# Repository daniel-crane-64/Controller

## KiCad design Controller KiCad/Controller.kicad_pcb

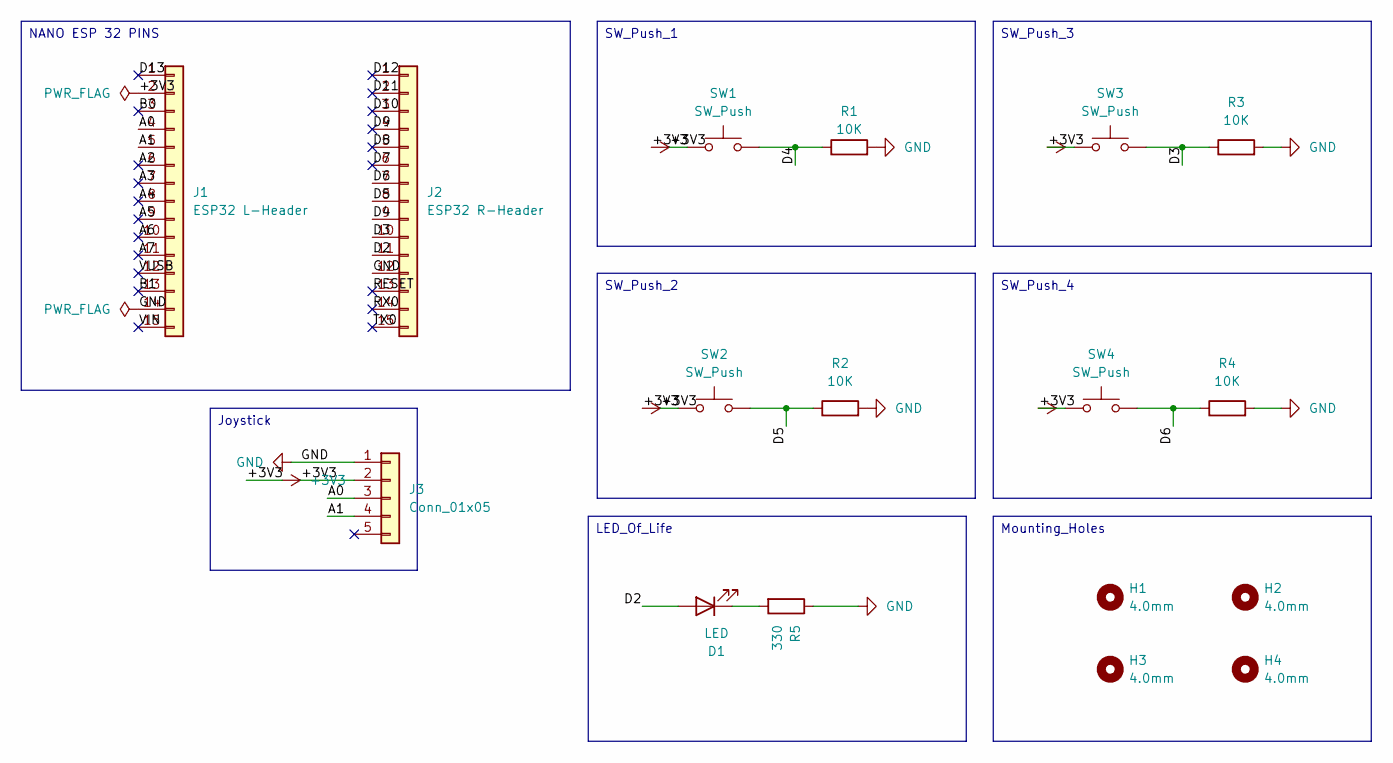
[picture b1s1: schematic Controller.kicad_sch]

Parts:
D1: LED; LED_D5.0mm
H1, H2, H3, H4: 4.0mm; MountingHole_4mm
J1: ESP32 L-Header; PinHeader_1x15_P2.54mm_Vertical
J2: ESP32 R-Header; PinHeader_1x15_P2.54mm_Vertical
J3: Conn_01x05; PinHeader_1x05_P2.54mm_Vertical
R1, R2, R3, R4: 10K; R_Axial_DIN0207_L6.3mm_D2.5mm_P7.62mm_Horizontal
R5: 330; R_Axial_DIN0207_L6.3mm_D2.5mm_P7.62mm_Horizontal
SW1, SW2, SW3, SW4: SW_Push; SW_PUSH_6mm

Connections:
+3V3: J1.2, J3.2, SW1.1, SW2.1, SW3.1, SW4.1
/A0: J1.4, J3.3
/A1: J1.5, J3.4
/A2: J1.6
/A3: J1.7
/A4: J1.8
/A5: J1.9
/A6: J1.10
/A7: J1.11
/B0: J1.3
/B1: J1.13
/D2: D1.2 (A), J2.11
/D3: J2.10, R3.1, SW3.2
/D4: J2.9, R1.1, SW1.2
/D5: J2.8, R2.1, SW2.2
/D6: J2.7, R4.1, SW4.2
/D7: J2.6
/D8: J2.5
/D9: J2.4
/D10: J2.3
/D11: J2.2
/D12: J2.1
/D13: J1.1
/RESET: J2.13
/RX0: J2.14
/TX0: J2.15
/VIN: J1.15
/VUSB: J1.12
GND: J1.14, J2.12, J3.1, R1.2, R2.2, R3.2, R4.2, R5.1
unnamed: D1.1 (K), R5.2

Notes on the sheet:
Mounting_Holes
SW_Push_4
LED_Of_Life
SW_Push_1
NANO ESP 32 PINS
SW_Push_3
Joystick
SW_Push_2

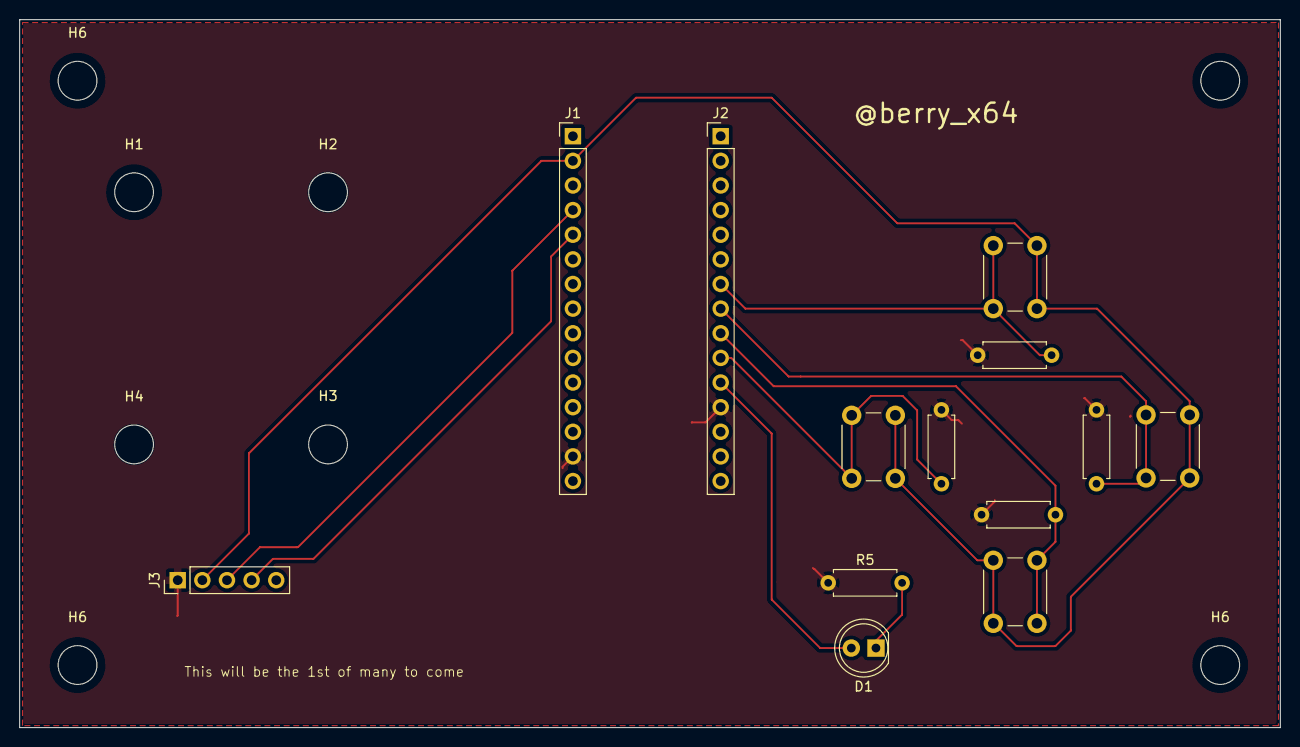
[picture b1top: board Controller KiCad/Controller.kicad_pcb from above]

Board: 2 copper layers, 130.0 x 73.0 mm, 21 parts (0 on the bottom side), 10 nets.

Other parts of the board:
H1#2, H6, H6#2, H6#3: 4.0mm; MountingHole_4mm

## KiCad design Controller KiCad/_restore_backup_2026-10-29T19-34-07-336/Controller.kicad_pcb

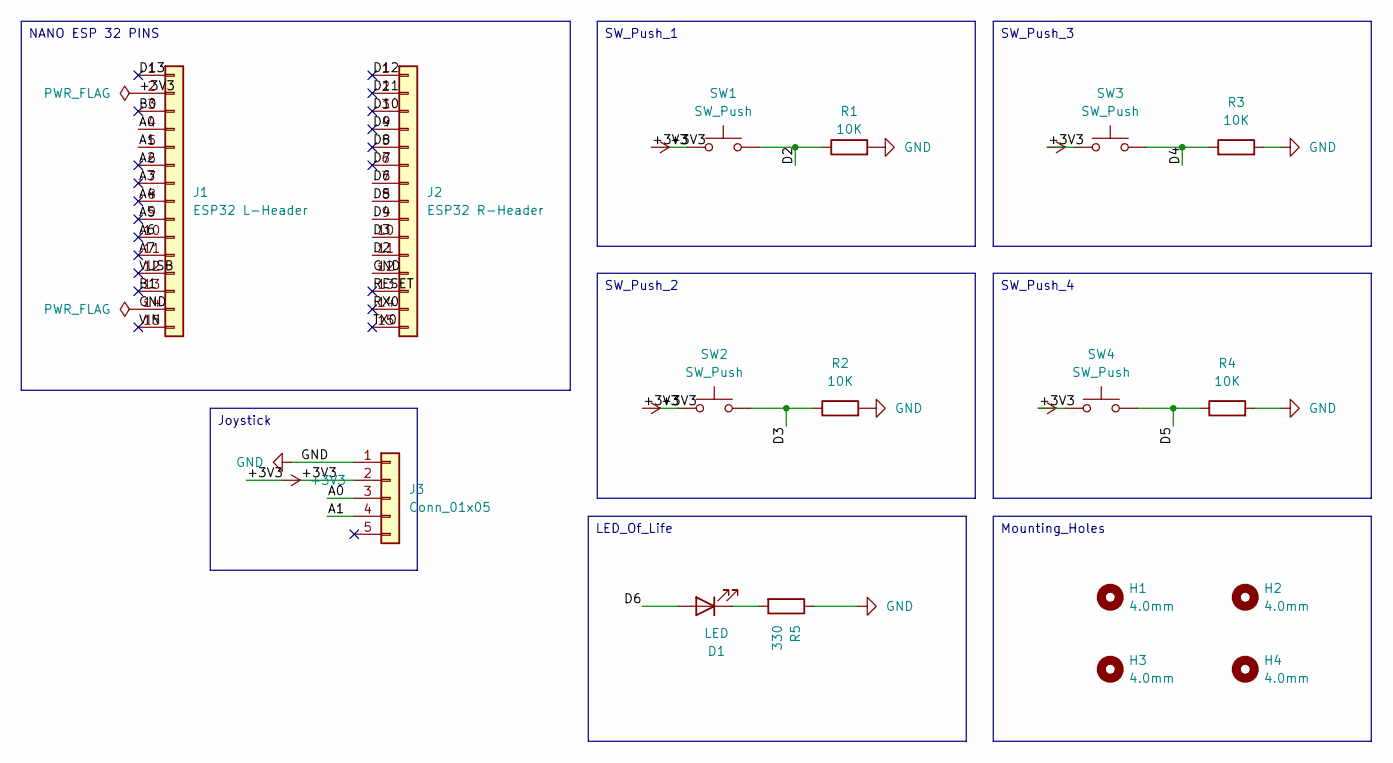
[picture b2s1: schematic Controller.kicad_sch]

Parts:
D1: LED; LED_D5.0mm
H1, H2, H3, H4: 4.0mm; MountingHole_4mm
J1: ESP32 L-Header; PinHeader_1x15_P2.54mm_Vertical
J2: ESP32 R-Header; PinHeader_1x15_P2.54mm_Vertical
J3: Conn_01x05; PinHeader_1x05_P2.54mm_Vertical
R1, R2, R3, R4: 10K; R_Axial_DIN0207_L6.3mm_D2.5mm_P7.62mm_Horizontal
R5: 330; R_Axial_DIN0207_L6.3mm_D2.5mm_P7.62mm_Horizontal
SW1, SW2, SW3, SW4: SW_Push; SW_PUSH_6mm

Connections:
+3V3: J1.2, J3.2, SW1.1, SW2.1, SW3.1, SW4.1
/A0: J1.4, J3.3
/A1: J1.5, J3.4
/A2: J1.6
/A3: J1.7
/A4: J1.8
/A5: J1.9
/A6: J1.10
/A7: J1.11
/B0: J1.3
/B1: J1.13
/D2: J2.11, R1.1, SW1.2
/D3: J2.10, R2.1, SW2.2
/D4: J2.9, R3.1, SW3.2 (2_2)
/D5: J2.8, R4.1, SW4.2 (2_2)
/D6: D1.2 (A), J2.7
/D7: J2.6
/D8: J2.5
/D9: J2.4
/D10: J2.3
/D11: J2.2
/D12: J2.1
/D13: J1.1
/RESET: J2.13
/RX0: J2.14
/TX0: J2.15
/VIN: J1.15
/VUSB: J1.12
GND: J1.14, J2.12, J3.1, R1.2, R2.2, R3.2, R4.2, R5.1
unnamed: D1.1 (K), R5.2

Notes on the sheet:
Mounting_Holes
SW_Push_4
LED_Of_Life
SW_Push_1
NANO ESP 32 PINS
SW_Push_3
Joystick
SW_Push_2

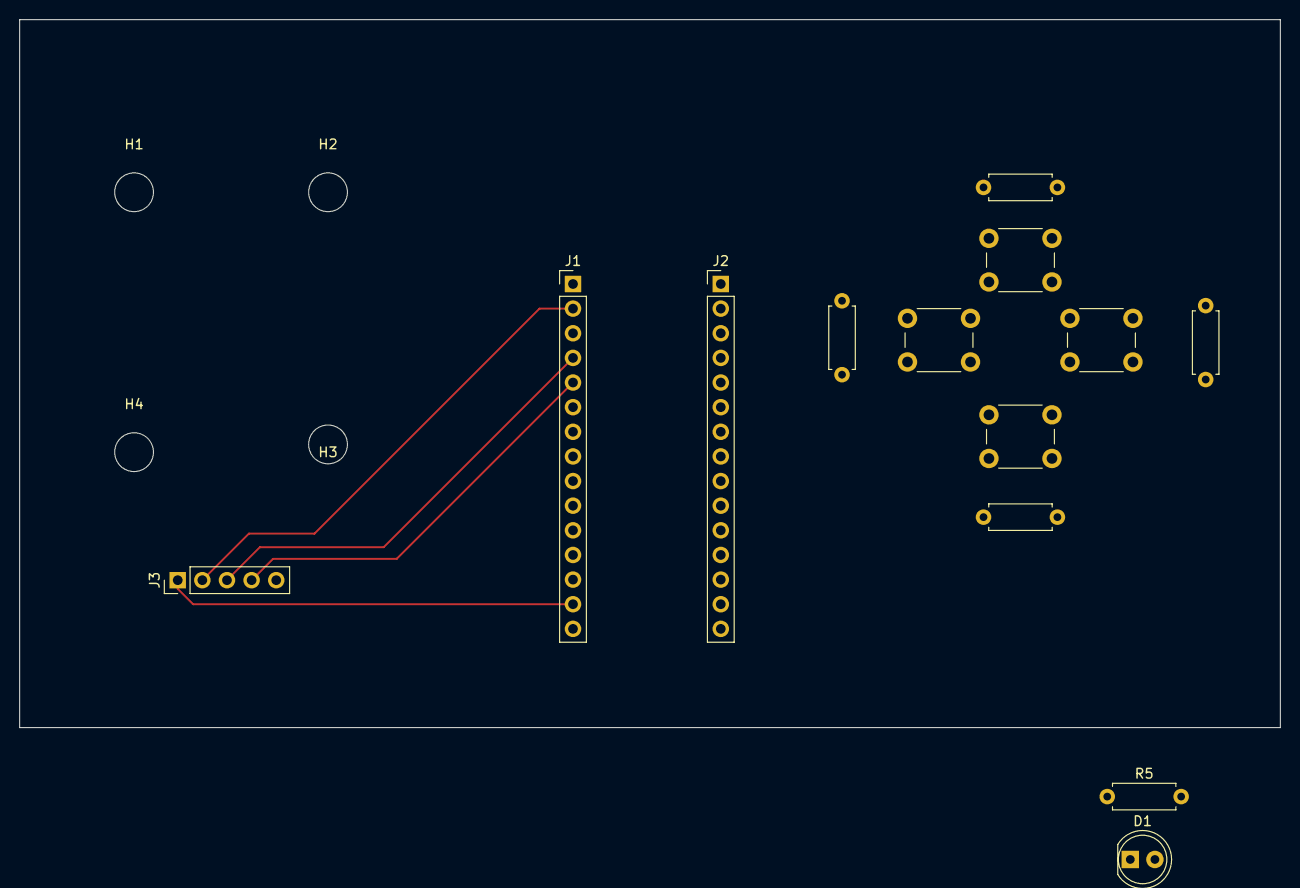
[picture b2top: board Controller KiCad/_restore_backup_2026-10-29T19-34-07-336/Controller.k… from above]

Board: 2 copper layers, 130.0 x 73.0 mm, 17 parts (0 on the bottom side), 10 nets.
